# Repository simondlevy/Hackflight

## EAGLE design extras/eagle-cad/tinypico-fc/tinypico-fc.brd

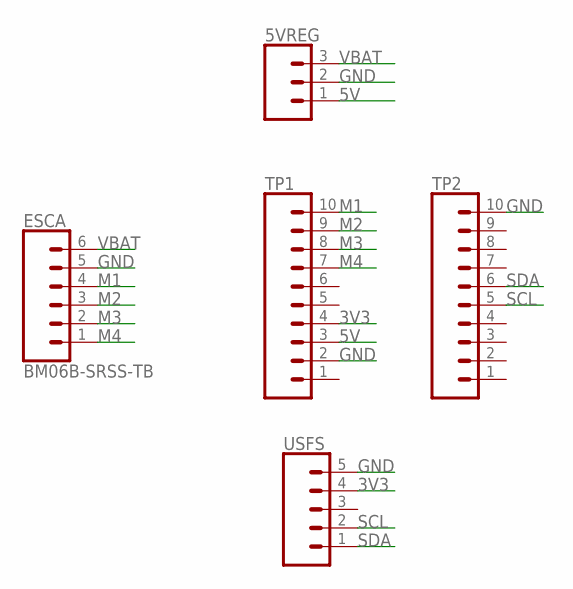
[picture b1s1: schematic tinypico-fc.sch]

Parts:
5VREG: CONN_031X03_NO_SILK; 1X03_NO_SILK
ESC: BM06B-SRSS-TB; JST-6-SMD-HORI-1.0MM
TP1, TP2: CONN_10NO_SILK_PTH_FEMALE; 1X10_NO_SILK
USFS: CONN_05NO_SILK; 1X05_NO_SILK

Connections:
3V3: TP1.4, USFS.4
5V: 5VREG.1, TP1.3
GND: 5VREG.2, ESC.5, TP1.2, TP2.10, USFS.5
M1: ESC.4, TP1.10
M2: ESC.3, TP1.9
M3: ESC.2, TP1.8
M4: ESC.1, TP1.7
SCL: TP2.5, USFS.2
SDA: TP2.6, USFS.1
VBAT: 5VREG.3, ESC.6

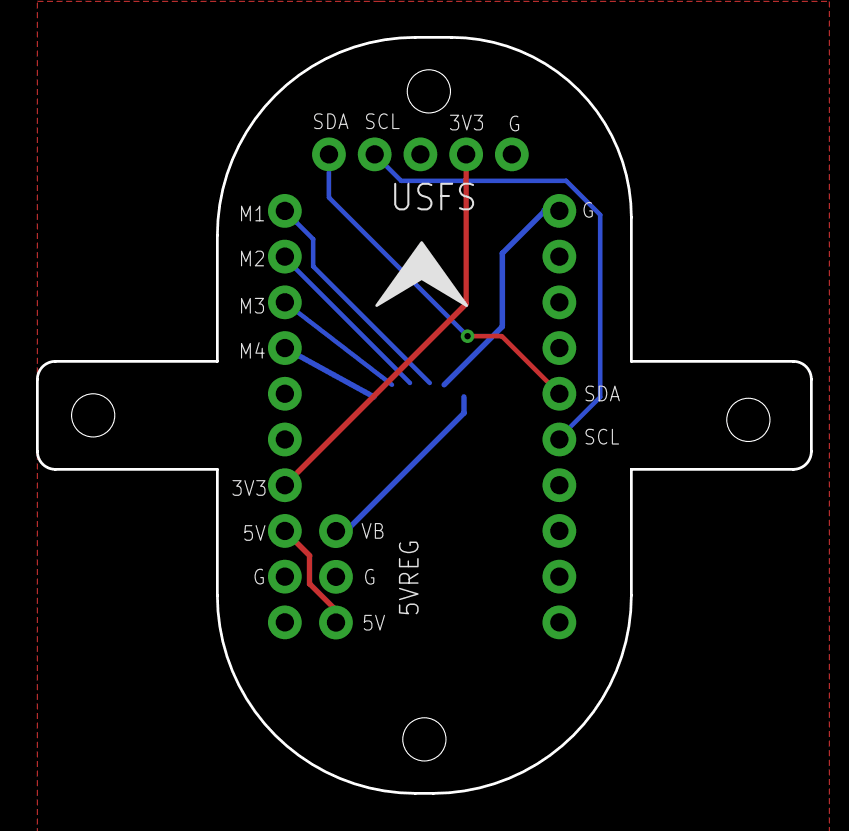
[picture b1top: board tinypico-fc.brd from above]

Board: 2 copper layers, 43.0 x 42.0 mm, 5 parts (1 on the bottom side), 10 nets.

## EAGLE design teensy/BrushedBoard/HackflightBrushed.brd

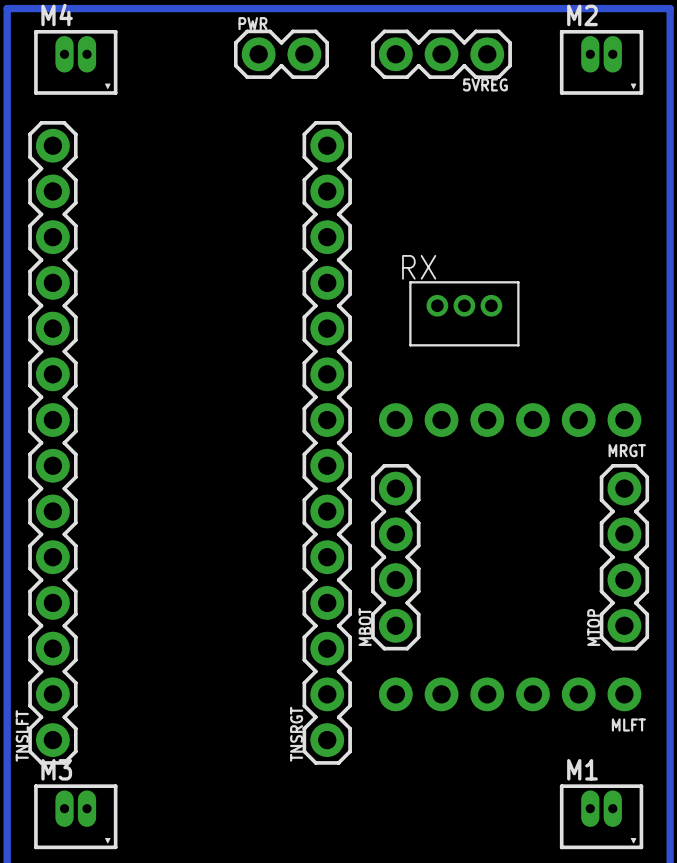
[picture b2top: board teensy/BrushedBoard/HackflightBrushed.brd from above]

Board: 2 copper layers, 13 parts (0 on the bottom side), 13 nets.

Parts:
5VREG: 1X03
M1, M2, M3, M4: 53047-0210
MBOT: 1X04
MLFT: 1X06_NO_SILK
MRGT: 1X06_NO_SILK
MTOP: 1X04
PWR: 1X02
RX: B3B-ZR
TNSLFT: 1X14
TNSRGT: 1X14

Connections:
3.3V: RX.1, TNSRGT.12
5VREG: 5VREG.1, TNSRGT.14
GND: 5VREG.2, M1.2, M2.2, M3.2, M4.2, MBOT.1, MBOT.4, MLFT.6, MTOP.1, MTOP.4, PWR.1, RX.2, TNSLFT.14
M1+: M1.1, MTOP.3
M1PWM: MRGT.2, TNSRGT.8
M2+: M2.1, MBOT.3
M2PWM: MLFT.2, TNSRGT.9
M3+: M3.1, MTOP.2
M3PWM: MLFT.1, TNSRGT.10
M4+: M4.1, MBOT.2
M4PWM: MRGT.3, TNSRGT.11
RX1: RX.3, TNSLFT.13
VBAT: 5VREG.3, MRGT.6, PWR.2

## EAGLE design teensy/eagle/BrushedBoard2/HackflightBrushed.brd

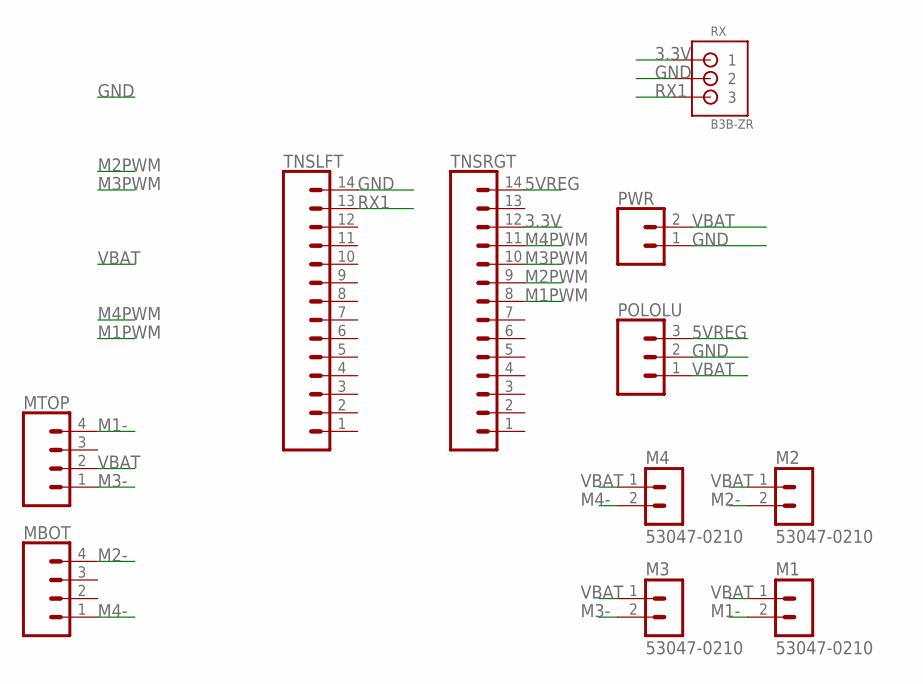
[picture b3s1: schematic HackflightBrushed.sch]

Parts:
M1, M2, M3, M4: 53047-0210
MBOT: CONN_04; 1X04
MTOP: CONN_04; 1X04
POLOLU: CONN_03; 1X03
PWR: CONN_02; 1X02
RX: B3B-ZR
TNSLFT: CONN_14; 1X14
TNSRGT: CONN_14; 1X14

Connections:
3.3V: RX.1, TNSRGT.12
5VREG: POLOLU.3, TNSRGT.14
GND: POLOLU.2, PWR.1, RX.2, TNSLFT.14
M1-: M1.2, MTOP.4
M1PWM: TNSRGT.8
M2-: M2.2, MBOT.4
M2PWM: TNSRGT.9
M3-: M3.2, MTOP.1
M3PWM: TNSRGT.10
M4-: M4.2, MBOT.1
M4PWM: TNSRGT.11
RX1: RX.3, TNSLFT.13
VBAT: M1.1, M2.1, M3.1, M4.1, MTOP.2, POLOLU.1, PWR.2

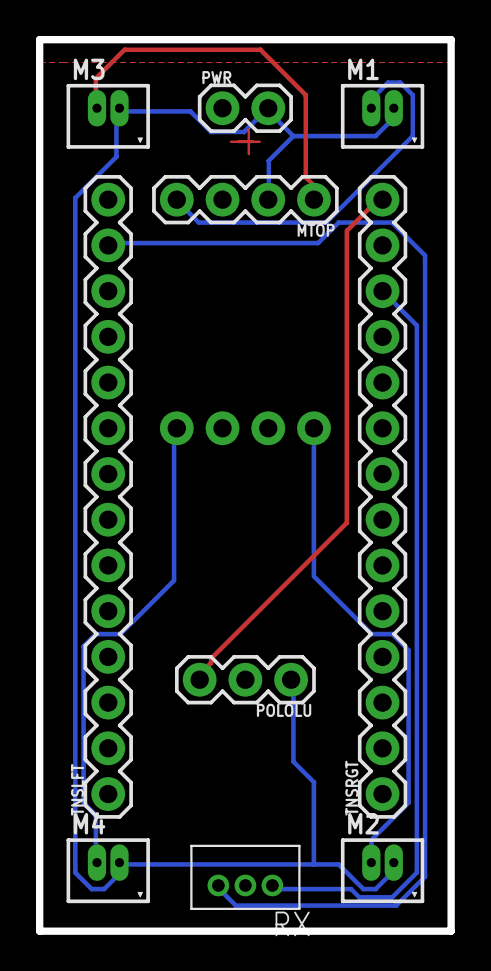
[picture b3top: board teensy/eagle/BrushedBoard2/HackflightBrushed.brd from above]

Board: 2 copper layers, 22.9 x 49.5 mm, 11 parts (1 on the bottom side), 9 nets.

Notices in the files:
parts and their libraries:
SparkFun-Connectors: Licensing: Creative Commons ShareAlike 4.0 International - https://creativecommons.org/licenses/by-sa/4.0
con-molex-picoblade: Copyright (C) 2010, Bob Starr
